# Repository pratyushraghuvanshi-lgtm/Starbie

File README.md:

# Starbie: Totoro the pocket pet

This is my Week 1 project for Hack Club's Half-Life. Starbie is a handheld virtual pet, like a Tamagotchi, that runs on a circuit board I designed myself. My pet's name is **Totoro**.

I had never done anything with hardware before this. I had never opened KiCad, never drawn a schematic, never written Arduino code and never used GitHub. Everything in this repo is the first time I have done it.

<!-- IMAGE: picture of the finished PCB (3D view or PCB editor screenshot) -->

## What it does

- Totoro walks back and forth across a small OLED screen with a sparkle trail blinking behind it, and its name sits in the top corner.
- **Button 1** opens a round menu with four choices: **NAP**, **PLAY**, **FEED** and **PET**. You tilt the board to roll a ball onto the choice you want, then press Button 1 again to confirm.
- Each choice changes Totoro's three stats (joy, energy and fullness) and plays a reaction: sleeping with little Zs, running laps, jumping, or hearts.
- **Button 2** shows the stats screen, with the temperature and humidity from the DHT11 sensor.
- Shaking the board wakes Totoro up and makes it happier.
- The stats are saved, so Totoro is the same after the power is turned off and on.

## Parts (BOM)

| Qty | Part | What it does |
|---|---|---|
| 1 | Seeed Studio XIAO ESP32-C3 | The brain. Runs the code. |
| 1 | 0.96" OLED display, 128x64, I2C (SSD1306) | The screen Totoro lives on. |
| 1 | MPU6050 module | Senses tilt and shaking. |
| 1 | DHT11 sensor | Measures temperature and humidity. |
| 1 | 10k resistor | Pull-up for the DHT11 data wire. |
| 2 | Cherry MX style switches | Button 1 and Button 2. |
| 1 | Custom PCB (this repo) | Holds and connects everything. |

## Wiring

| Part | Pin on the part | XIAO pin | Number in the code |
|---|---|---|---|
| OLED and MPU6050 | SCL | D4 | GPIO 6 |
| OLED and MPU6050 | SDA | D5 | GPIO 7 |
| DHT11 | DATA (with 10k pull-up to 3.3V) | D1 | GPIO 3 |
| Button 1 | one side (other side to GND) | D2 | GPIO 4 |
| Button 2 | one side (other side to GND) | D3 | GPIO 5 |
| All modules | power and ground | 3V3 and GND | not in the code |

<!-- IMAGE: screenshot of the schematic -->

## Software I used

- **KiCad 10**: drawing the schematic, laying out the PCB, running the design rules check and exporting the Gerber files.
- **KiCad Image Converter**: turning my pictures into silkscreen art for the board.
- **Arduino IDE 2**: editing and compiling the firmware.
- **image2cpp**: turning a picture into the 32x32 pixel sprite for Totoro.
- **GitHub**: hosting this repo.
- **Claude**: the guide was hard for me to follow at first, so I had Claude turn it into smaller steps and help me understand my errors.

Arduino libraries: Adafruit GFX, Adafruit SSD1306, Adafruit MPU6050 and DHT sensor library. Board package: esp32 by Espressif, with the board set to XIAO_ESP32C3.

## What I changed from the guide

- **Board art**: I added my own silkscreen art (Attack on Titan fan art, including the Wings of Freedom emblem) and my name.
- **The pet**: I replaced the default sprite with my own 32x32 creature.
- **The name**: the screen shows "Totoro" in the top corner.
- **Sparkle trail**: a small sparkle blinks behind Totoro while it walks.
- **Pin numbers**: on my board SDA is on D5 and SCL is on D4, so the code uses `I2C_SDA_PIN = 7` and `I2C_SCL_PIN = 6`.

<!-- IMAGE: close-up of the silkscreen art -->

## How I built it

1. Installed KiCad and added the symbol and footprint libraries from the Half-Life care package.
2. Drew the schematic: the XIAO, the screen, the motion sensor, the DHT11 with its resistor and the two buttons, connected with net labels.
3. Gave every symbol a footprint, which is the real copper shape the part gets soldered onto.
4. Moved everything into the PCB editor, drew the star outline on the Edge.Cuts layer and arranged the parts inside it.
5. Routed every connection as a copper track and added a ground fill on the back of the board.
6. Ran the design rules check and fixed errors until only the two that the guide says are expected were left.
7. Added my art and name on the silkscreen layer.
8. Set up Arduino IDE, changed the code to make the pet mine, and compiled it.
9. Exported the Gerber and drill files and zipped them.

<!-- IMAGE: PCB editor screenshot showing the routed tracks -->

## What was hard

This was very challenging because every single part of it was new to me. Some of the things I got stuck on:

- **Getting started.** I spent most of the first hour stuck before I had even placed a part. The KiCad download link I tried gave a 404, I was not sure the mirror was safe, and I did not know which folder the library files were supposed to go in.
- **Not knowing the words.** Symbol, footprint, net label, Gerber, repo. I had to learn what each one meant before the steps made sense.
- **SDA and SCL.** The guide's schematic and the guide's code did not agree about which pin was which. I followed the schematic, then had to change two numbers in the code so it matched my board.
- **The design rules check.** My first check had 10 errors. One track ended on the wrong pad, which shorted two signals together. Three connections were missing and I had no ground fill yet. I fixed them one at a time and got down to the 2 expected errors.
- **Code that would not compile.** I pasted new lines into the middle of another line and broke it. I also got a "Missing FQBN" error, which only meant I had not picked a board yet.
- **The sprite.** The first version came out with the colors inverted and one row short (32x31 instead of 32x32).
- **Files and folders.** Arduino would not let me save the sketch into a folder inside itself, and at one point I thought I had deleted all my code while moving it.

It was very hard and took multiple attempts as you can see from the images above

## What I learned

- A schematic is the plan and a PCB is the real thing. The schematic says what connects to what, and the PCB is where the copper actually goes.
- One pin can have two names. D4 is printed on the XIAO, but the code calls the same pin GPIO 6.
- Net labels with the same name are connected even when no wire is drawn between them, so the spelling has to match exactly.
- The design rules check finds mistakes I could not see by looking, like a track touching the wrong pad.
- A ground fill connects every ground pin without drawing each track by hand.
- Reading an error message slowly usually tells you what is wrong.
- Save often, and copy files instead of moving them.

## What's in this repo

```
PCB/        KiCad project, schematic and board files
Gerbers/    zipped Gerber and drill files, ready to send to a board maker
Firmware/   Starbie/Starbie.ino, the Arduino code
```

Made by Pratyush Raghuvanshi.
## Credits

Built for [Hack Club Half-Life](https://hackclub.com), following the Starbie guide by SharKingStudios. Attack on Titan belongs to its creators; the board art is fan art.

Made by Pratyush Raghuvanshi.

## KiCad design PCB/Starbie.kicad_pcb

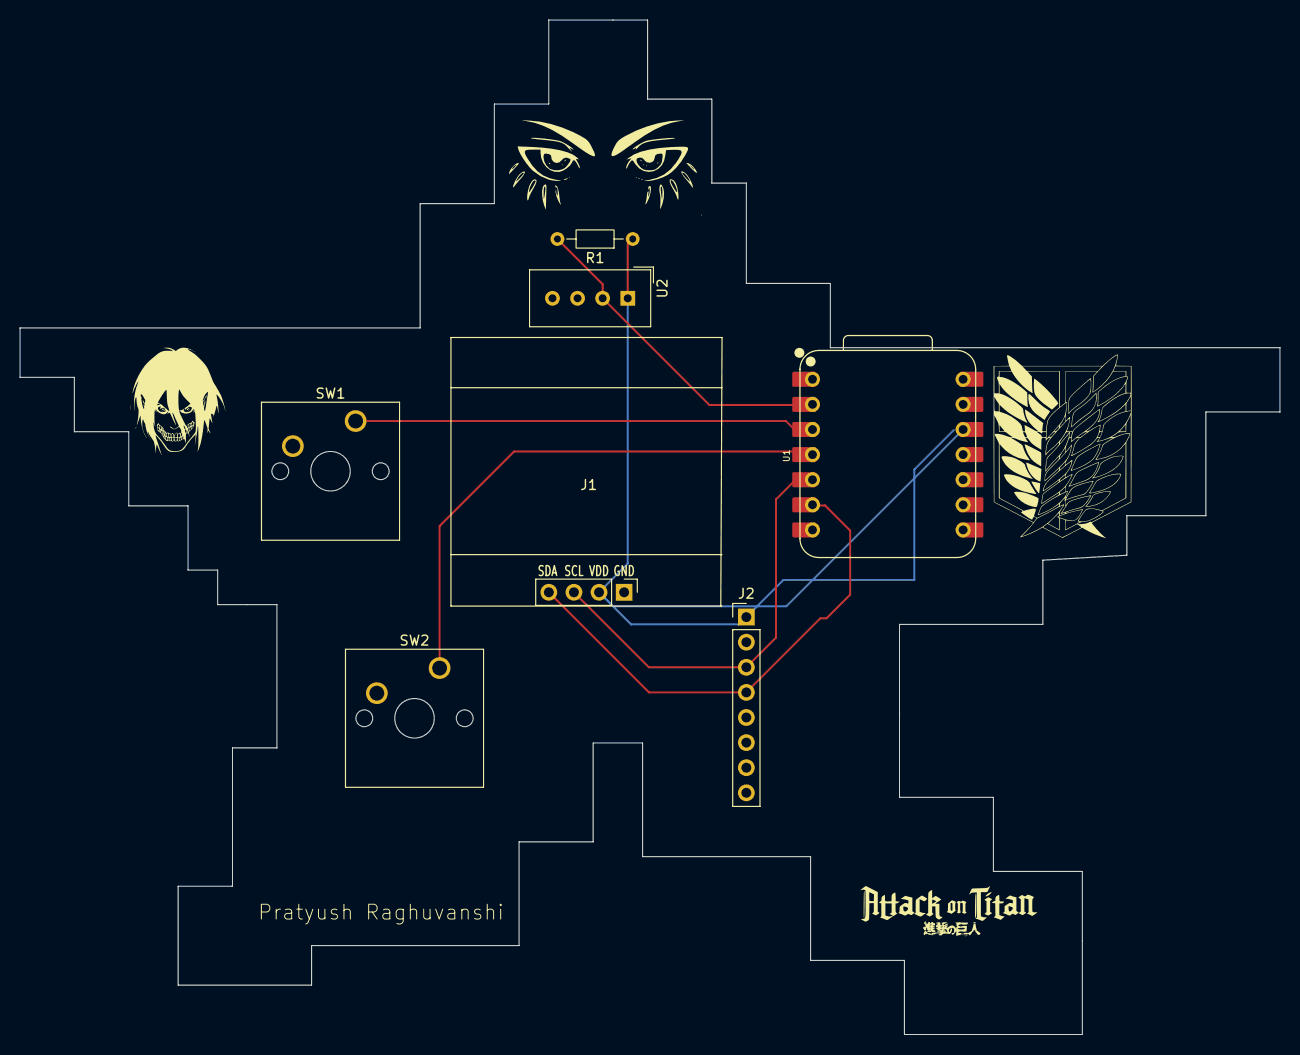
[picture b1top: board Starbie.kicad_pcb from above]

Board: 2 copper layers, 127.5 x 102.7 mm, 7 parts (0 on the bottom side), 7 nets.

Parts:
J1: Conn_01x04_Pin; Display_128x64_096_I2C
J2: Conn_01x08_Pin; PinHeader_1x08_P2.54mm_Vertical
R1: 10k; R_Axial_DIN0204_L3.6mm_D1.6mm_P7.62mm_Horizontal
SW1, SW2: SW_Push; SW_Cherry_MX_1.00u_PCB
U1: XIAO-ESP32-C3-SMD; XIAO-ESP32-C6-DIP
U2: DHT11; Aosong_DHT11_5.5x12.0_P2.54mm

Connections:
+3.3V: J1.2, J2.1, R1.1, U1.12 (3V3_OUT), U2.1 (VDD)
/DHT11 DATA: R1.2, U1.2 (D1), U2.2 (DATA)
/GPI02: SW1.1, U1.3 (D2)
/GPI03: SW2.1, U1.4 (D3)
/SCL: J1.3, J2.3, U1.5 (D4)
/SDA: J1.4, J2.4, U1.6 (D5)
GND: J1.1, J2.2, SW1.2, SW2.2, U1.13 (GND), U2.4 (GND)
